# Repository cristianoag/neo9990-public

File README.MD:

# NEO9990

**NEO9990** is an open-hardware V9990 video-cartridge project for the MSX computer system. 

## Why NEO9990?

The Yamaha V9990 (the "E-VDP III") was designed in the early 1990s for the MSX3 standard that never reached the market. Its best-known home is the Sunrise GFX9000 cartridge from 1994, which gave MSX computers 2D graphics well beyond the built-in VDP, with high-resolution bitmap and tile modes and a hardware command engine. Its software library is small, and every title depends on that one chip.

[TRH9000](https://github.com/cristianoag/trh9000) was my first step: an open-source, real-chip GFX9000-compatible cartridge, documented so that anyone can build one. It works, but it relies on the Yamaha V9990 itself, and those chips are now super rare. They have been out of production for decades, and every cartridge built consumes a part that cannot be replaced. A design that needs one chip per board cannot be reproduced by the community at any useful scale, so we were kind of forced to develop emulation hardware.

NEO9990 is the answer to that shortage. Instead of hunting for scarce silicon, the emulation boards **reproduce the V9990 in firmware** on readily available, modern hardware, keeping the MSX side as close to the original as possible: the same I/O ports (60h–6Fh), the same register model and the same VRAM behaviour. Video output is digital (HDMI/DVI) rather than 15 kHz analog RGB, so it works with current displays.

NEO9990 is an open-source project and another contribution to the MSX community from **The Retro Hacker**. Build it, improve it, port it, and share what you learn.

## Implementation tracks

This repository holds three implementation tracks, from the original real-chip design to the emulation boards that remove the dependency on the V9990 supply:

| Implementation | Approach | Status |
| --- | --- | --- |
| [Real-chip](hardware/realchip/) | Uses a Yamaha V9990 and a dedicated HDMI conversion/output stage. | Hardware design and fabrication files are published. |
| [Orange Pi](hardware/orangepi/) | Replaces V9990 hardware with V9990 emulation on an Orange Pi Zero 2W, connected to the MSX bus through a CPLD. | Prototype; backed by test firmware, HDL, and protocol software. Not a finished cartridge. |
| [Core2350B](hardware/core2350b/) | Replaces V9990 hardware with emulation on a Waveshare Core2350B (RP2350B) wired directly to the MSX bus, with HSTX HDMI/DVI output and USB-C. | Rev 1.0 schematic, routed PCB and initial tests done. V9990 firmware v1.00. |

|  |  |
|:---:|:---:|
| Real-chip board, front | Real-chip board, rear |

|  |  |
|:---:|:---:|
| Orange Pi prototype rendering, front | Orange Pi prototype rendering, rear |

|  |  |
|:---:|:---:|
| Core2350B board rendering, front | Core2350B board rendering, rear |

## Implementations in this repository

### Real-chip NEO9990

The real-chip implementation is the hardware project under [`hardware/realchip`](hardware/realchip/). It uses the Yamaha V9990 device and includes a chip-based digital-video conversion stage for HDMI output.

- [Real-chip overview](docs/realchip.md)
- [KiCad project](hardware/realchip/neo9990/neo9990.kicad_pro)
- [KiCad schematic](hardware/realchip/neo9990/neo9990.kicad_sch)
- [KiCad PCB](hardware/realchip/neo9990/neo9990.kicad_pcb)
- [Production files](hardware/realchip/neo9990/production/)
- [Interactive BOM](hardware/realchip/neo9990/bom/ibom.html)

### Orange Pi NEO9990

The Orange Pi implementation is an experimental board under [`hardware/orangepi`](hardware/orangepi/). It targets bare-metal V9990 emulation on an Orange Pi Zero 2W and uses an EPM7160STC100-10 CPLD between the MSX bus and a 16-bit parallel GPIO mailbox.

The full MSX address bus, memory request, and slot select signals are available to the host for ROM and mapper services. CPLD profiles prepare V9990, ROM, and OPL4 decoding, although the current firmware implements only a limited V9990 bring-up subset.

- [Orange Pi overview (hardware and software)](docs/orangepi.md)
- [KiCad prototype project](hardware/orangepi/neo9990/neo9990.kicad_pro)
- [Prototype restrictions and validation notes](hardware/orangepi/neo9990/prototype-notes.txt)
- [GPIO assignment](hardware/orangepi/neo9990/gpio-map.csv)
- [Prototype BOM](hardware/orangepi/neo9990/bom.csv)
- [Assembly drawings](hardware/orangepi/neo9990/plots/)
- [3D previews](hardware/orangepi/neo9990/plots/prototype-3d.png)
- [CPLD source and protocol documentation](software/orangepi/cpld/README.txt)
- [Parallel host ABI](software/orangepi/host/README.txt)
- [Bare-metal bring-up firmware](software/orangepi/firmware/README.txt)

### Core2350B NEO9990

The Core2350B implementation is under [`hardware/core2350b`](hardware/core2350b/). A Waveshare Core2350B module is wired directly to the MSX slot without voltage translation, outputs HDMI/DVI from the RP2350 HSTX pins, and is programmed over USB-C. The board outline, edge connector and USB-C wiring come from the PicoVerse 2350 board.

Rev 1.0 has a finished schematic and a routed PCB, and initial tests have been done. The V9990 firmware builds with `make` from `software/core2350b/v9990`; the UF2 file is in [`firmware/`](firmware/).

- [Core2350B hardware](docs/core2350b-hardware.md)
- [Core2350B firmware](docs/core2350b-firmware.md)
- [KiCad project](hardware/core2350b/neo9990/neo9990.kicad_pro)
- [GPIO assignment](hardware/core2350b/neo9990/gpio-map.csv)

## Documentation

The explanatory documents for every implementation are in [`docs/`](docs/index.md).

## Repository layout

```text
docs/          documentation for each implementation
firmware/      ready-to-flash Core2350B firmware images (UF2)
hardware/
  realchip/    Yamaha V9990 implementation and HDMI conversion/output hardware
  orangepi/    Orange Pi Zero 2W / CPLD prototype
  core2350b/   Waveshare Core2350B (RP2350B) implementation
software/
  orangepi/    CPLD, host protocol, and firmware tests/supporting software
  core2350b/   V9990 firmware for the Core2350B board
```

Each implementation keeps its own hardware and implementation-specific software. Files under `software/orangepi` are the supporting prototype software for `hardware/orangepi`; they are not firmware for the real-chip board or the Core2350B board.

## Contributing

Contributions are welcome through issues and pull requests. Keep changes scoped to the correct implementation directory and state clearly whether they affect the real-chip board, the Orange Pi prototype, or a future track.

Hardware changes should include the corresponding fabrication/CAD outputs when applicable. Prototype software and HDL changes should include focused tests and should not claim unverified board-level operation.

## Sponsoring

You can support NEO9990 development through [GitHub Sponsors](https://github.com/sponsors/cristianoag).

## Third-party notices and references

The NEO9990 Core2350B firmware (`software/core2350b`) builds on the work below.
Source files that derive from it say so in their header comment.

* **Yamaha V9990 behaviour: openMSX**: Where the Yamaha V9990 Application Manual is silent, the V9990 core follows the
behaviour of openMSX (`src/video/v9990`, <https://github.com/openMSX/openMSX>), which is released under the GNU General Public License v2.

* **DVI output: pico-examples**: `common/dvi_out.c` is derived from the HSTX DVI example in <https://github.com/raspberrypi/pico-examples>. Copyright 2020 (c) Raspberry Pi (Trading) Ltd.

## License

This project is licensed under the [Creative Commons Attribution-NonCommercial-ShareAlike 4.0 International License](http://creativecommons.org/licenses/by-nc-sa/4.0/).

- You may remix and adapt the material with proper attribution.
- Derivative works must be shared under the same license.
- Commercial use is not permitted without explicit authorization.

See [LICENSE.txt](LICENSE.txt) for the complete license text.

The Orange Pi firmware and shared host protocol header are separately licensed under **GPL-2.0-only**. See the [firmware license and notices](software/orangepi/firmware/COPYING) and [openMSX provenance](software/orangepi/firmware/third_party/openmsx/PROVENANCE.txt).

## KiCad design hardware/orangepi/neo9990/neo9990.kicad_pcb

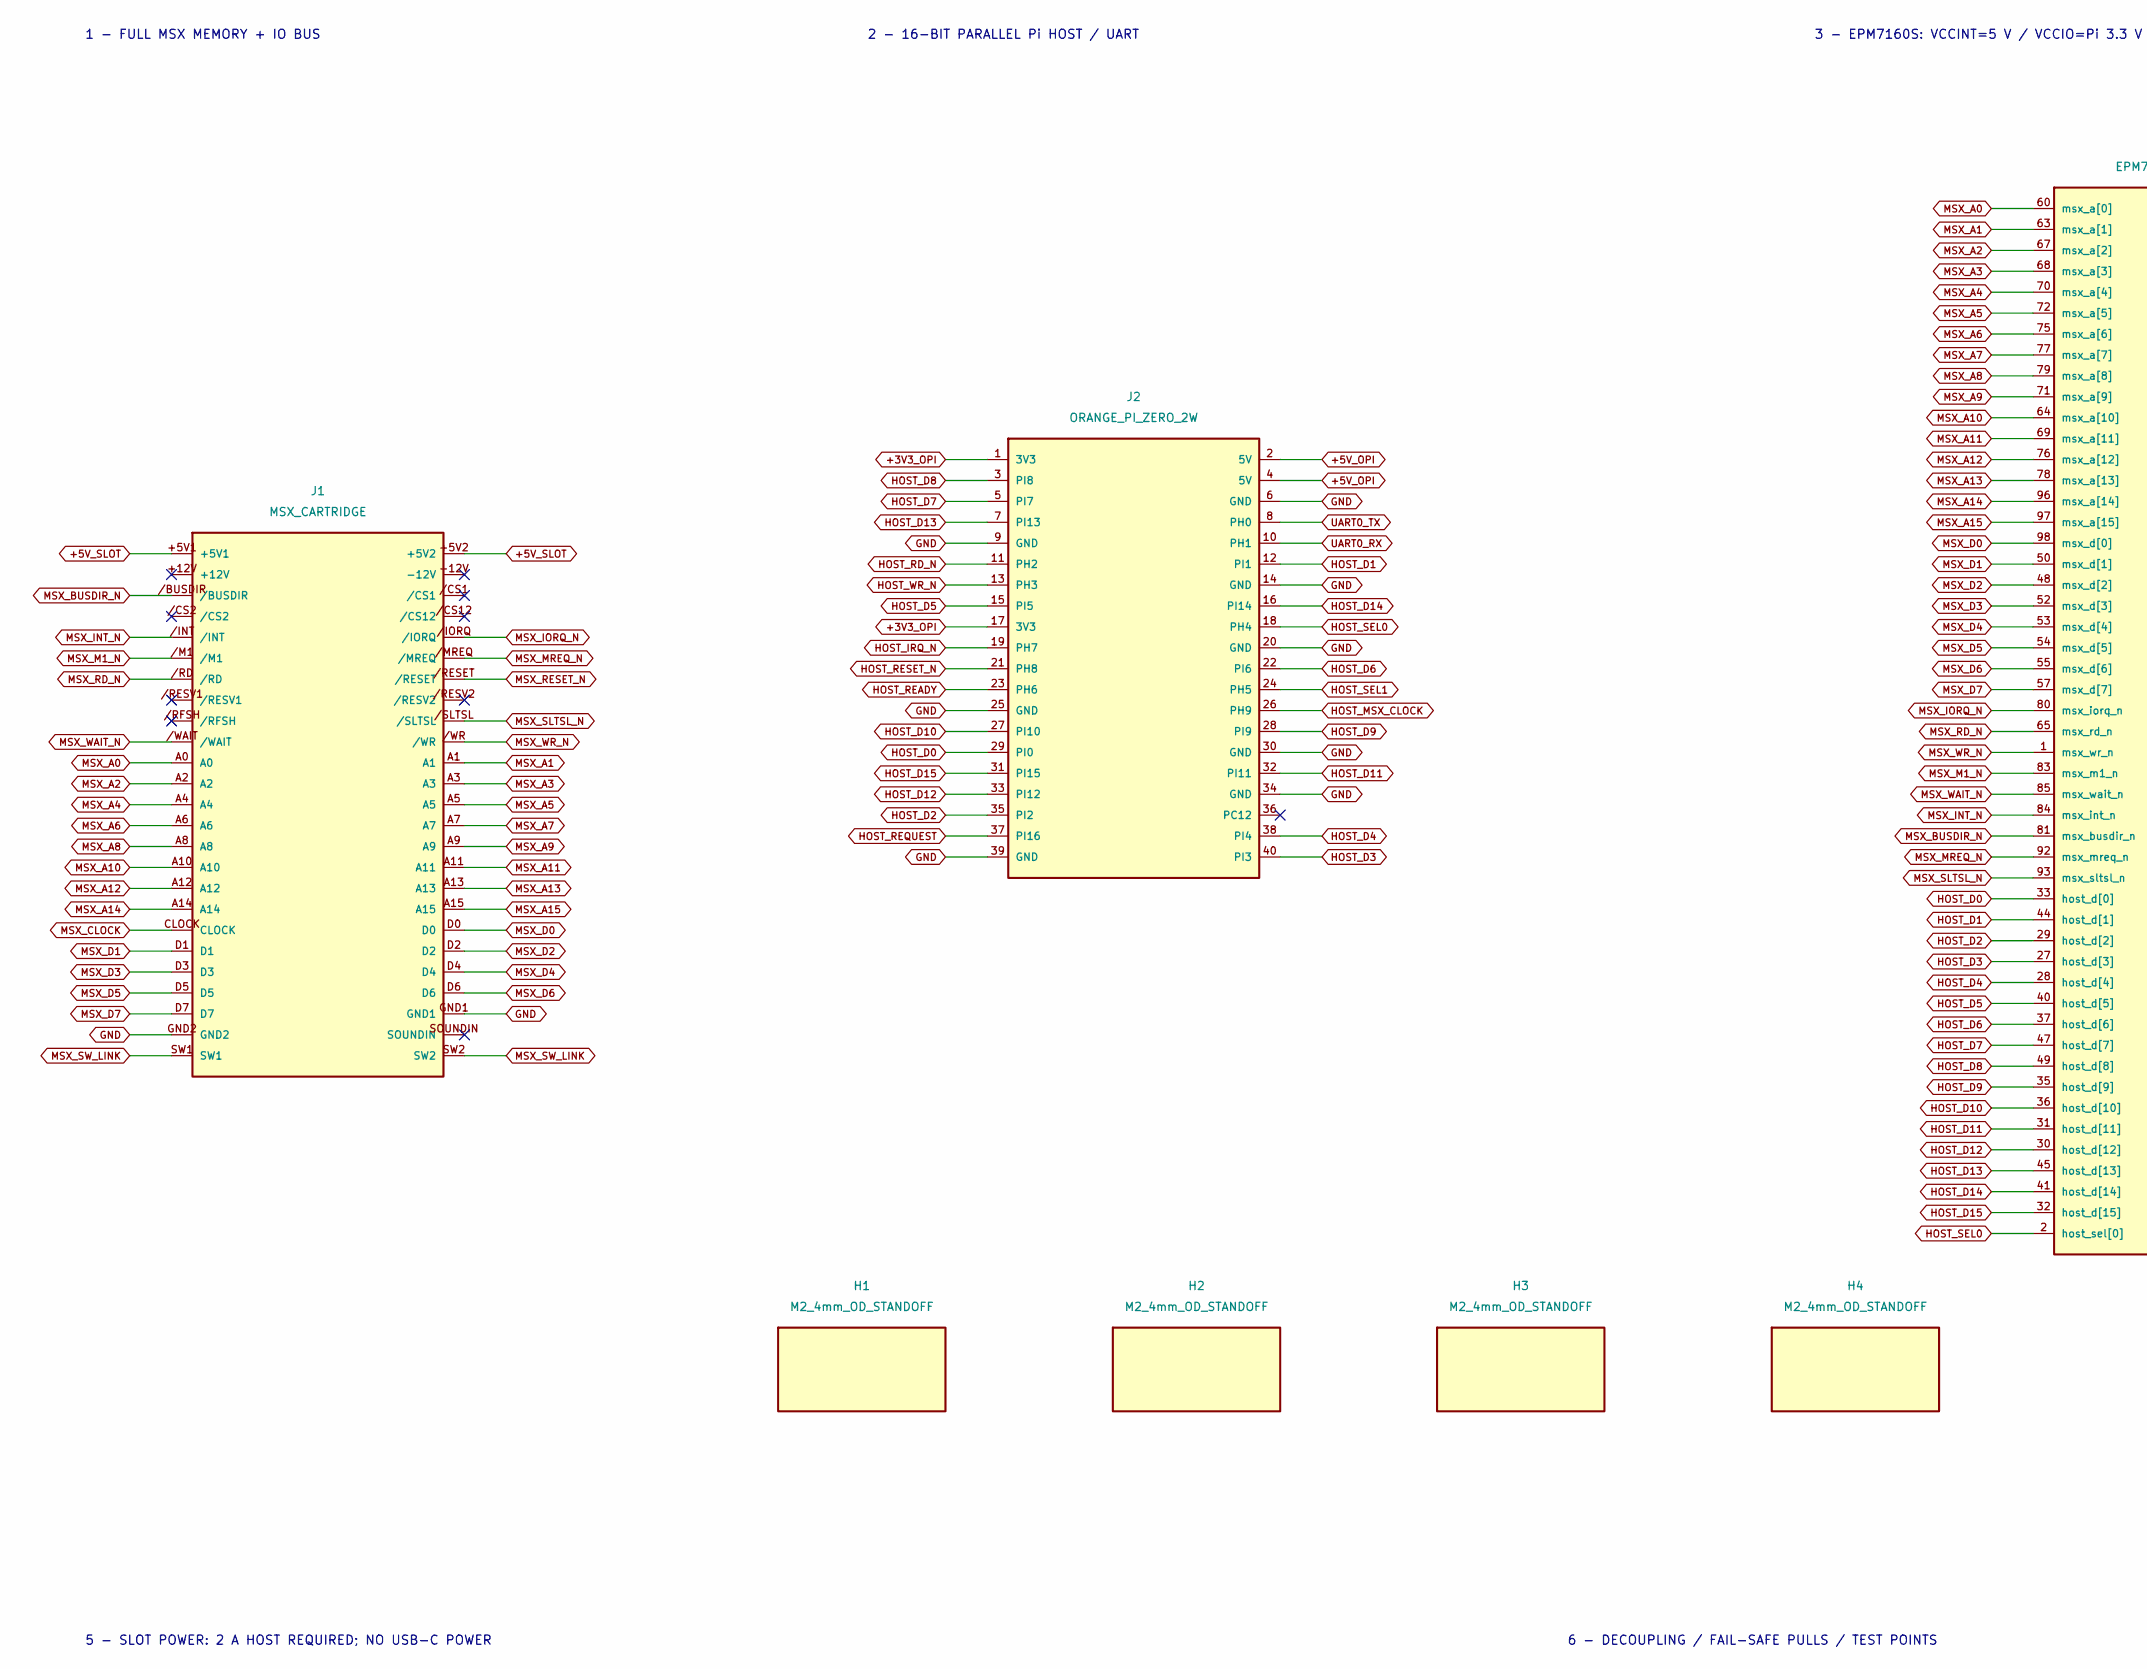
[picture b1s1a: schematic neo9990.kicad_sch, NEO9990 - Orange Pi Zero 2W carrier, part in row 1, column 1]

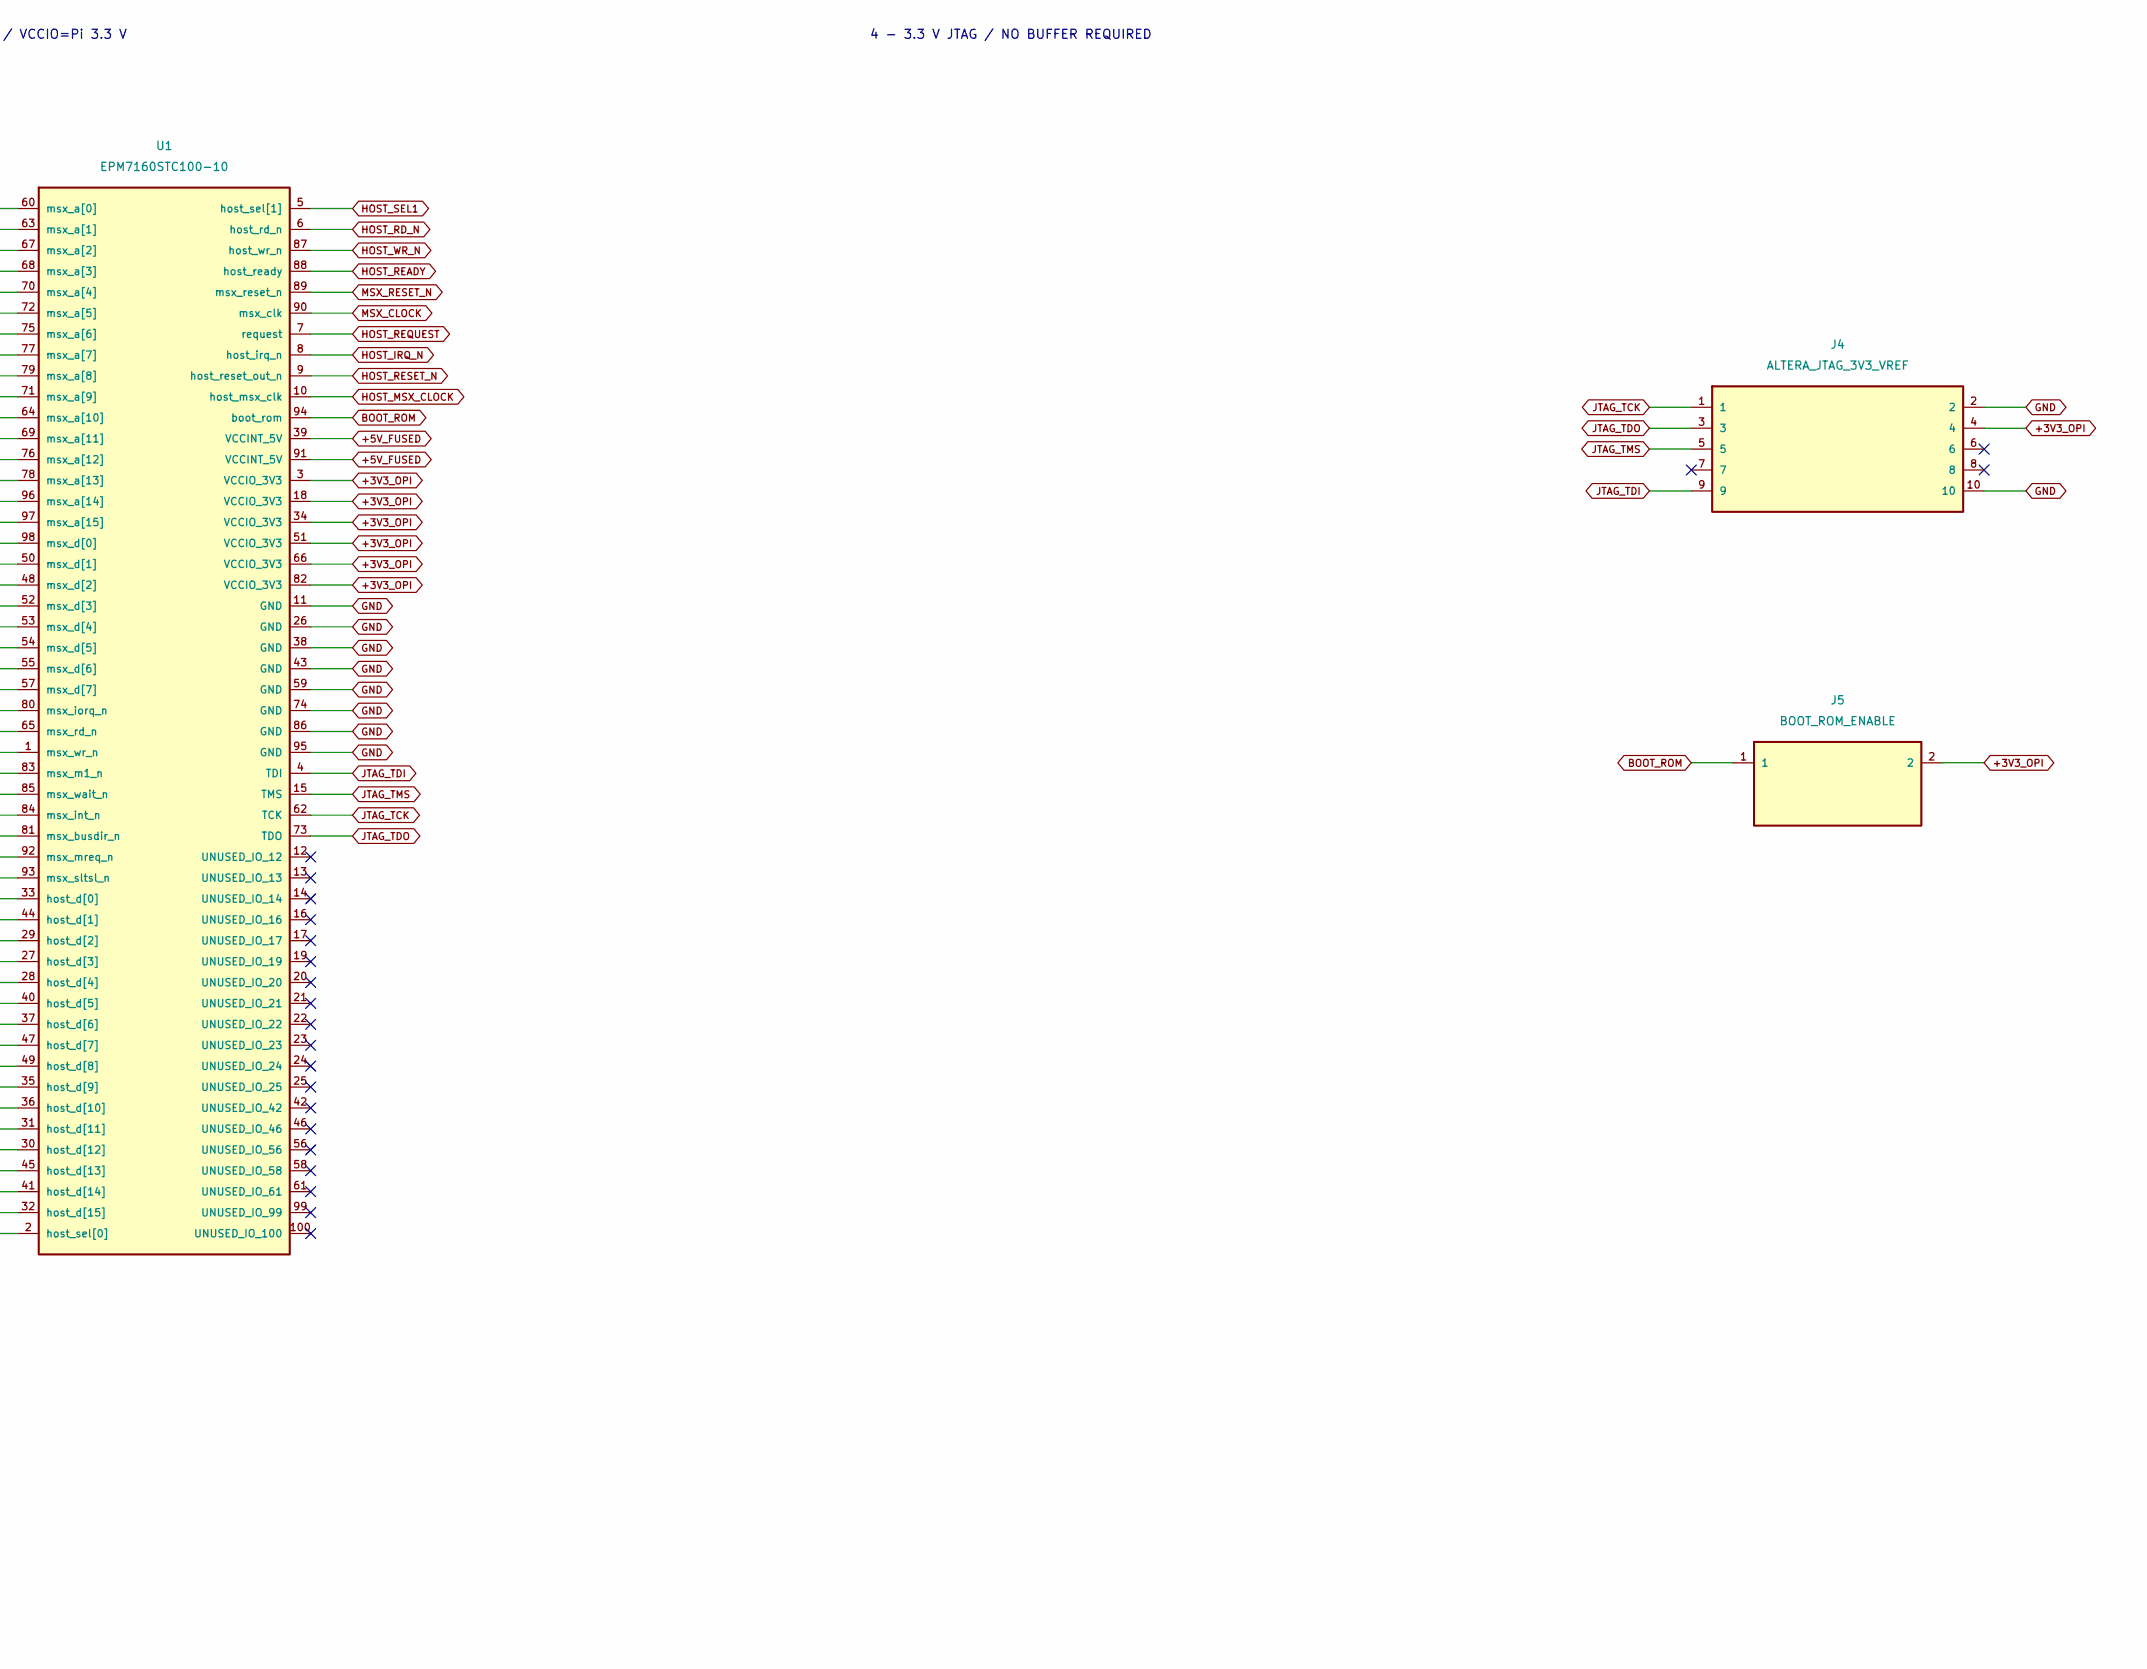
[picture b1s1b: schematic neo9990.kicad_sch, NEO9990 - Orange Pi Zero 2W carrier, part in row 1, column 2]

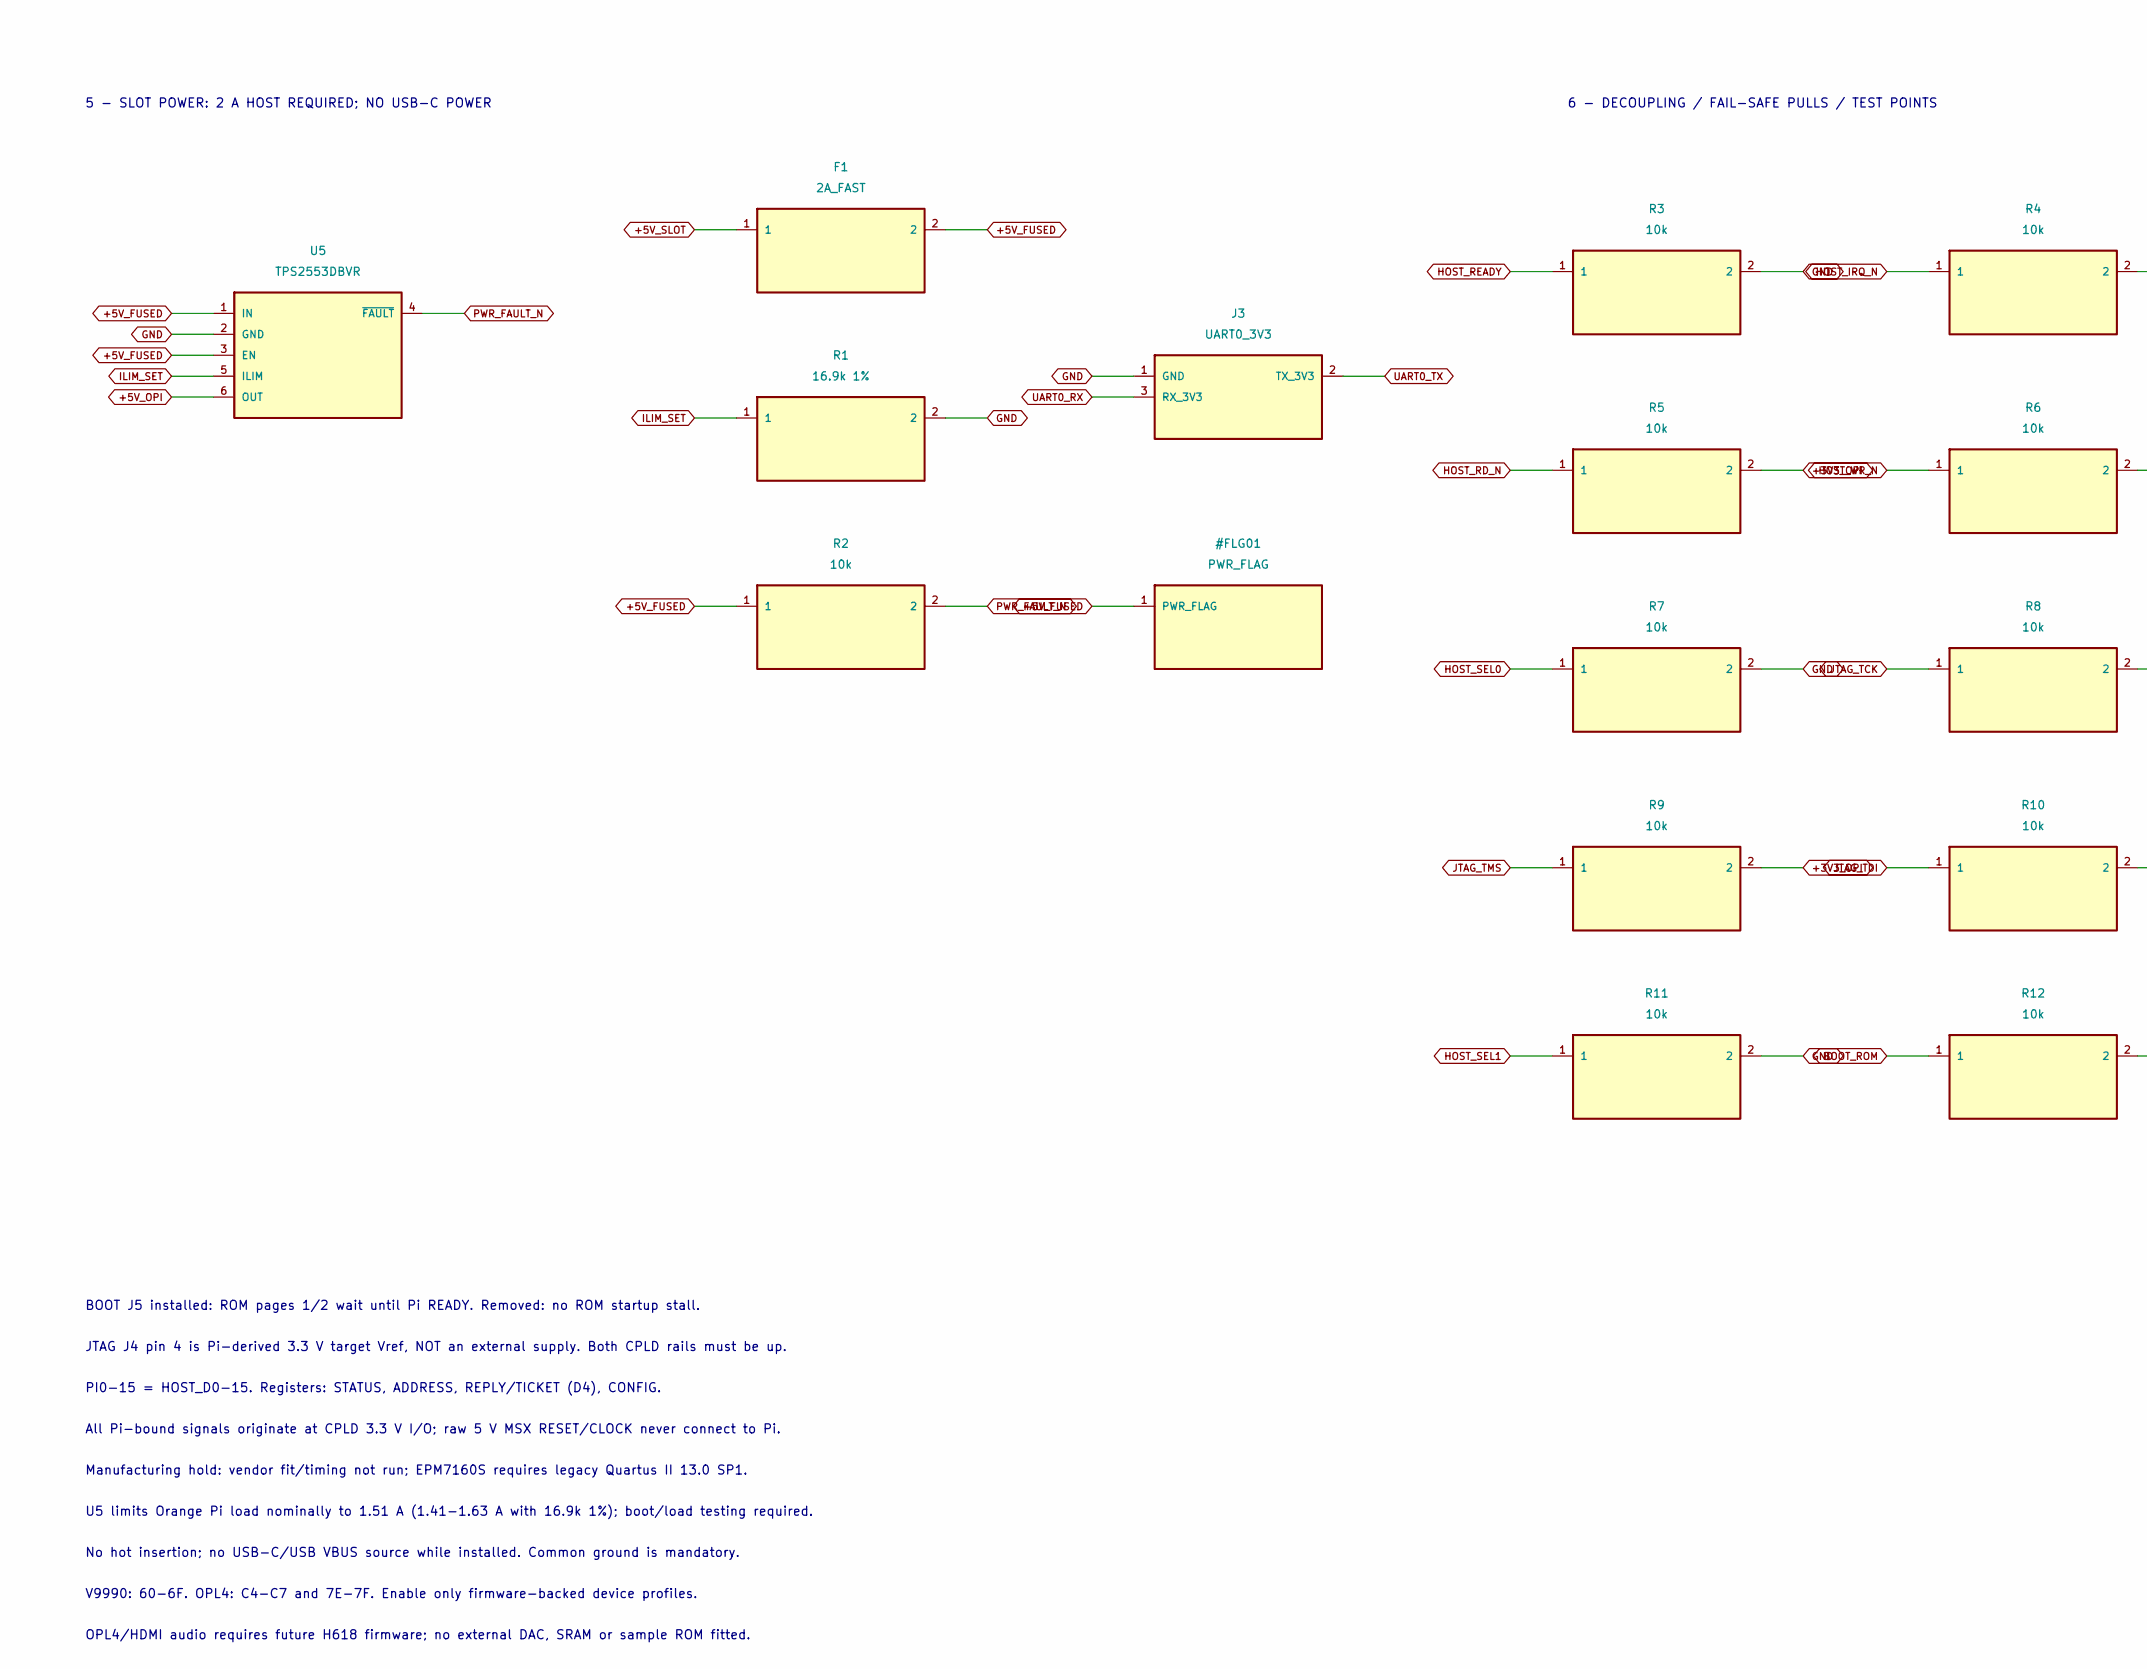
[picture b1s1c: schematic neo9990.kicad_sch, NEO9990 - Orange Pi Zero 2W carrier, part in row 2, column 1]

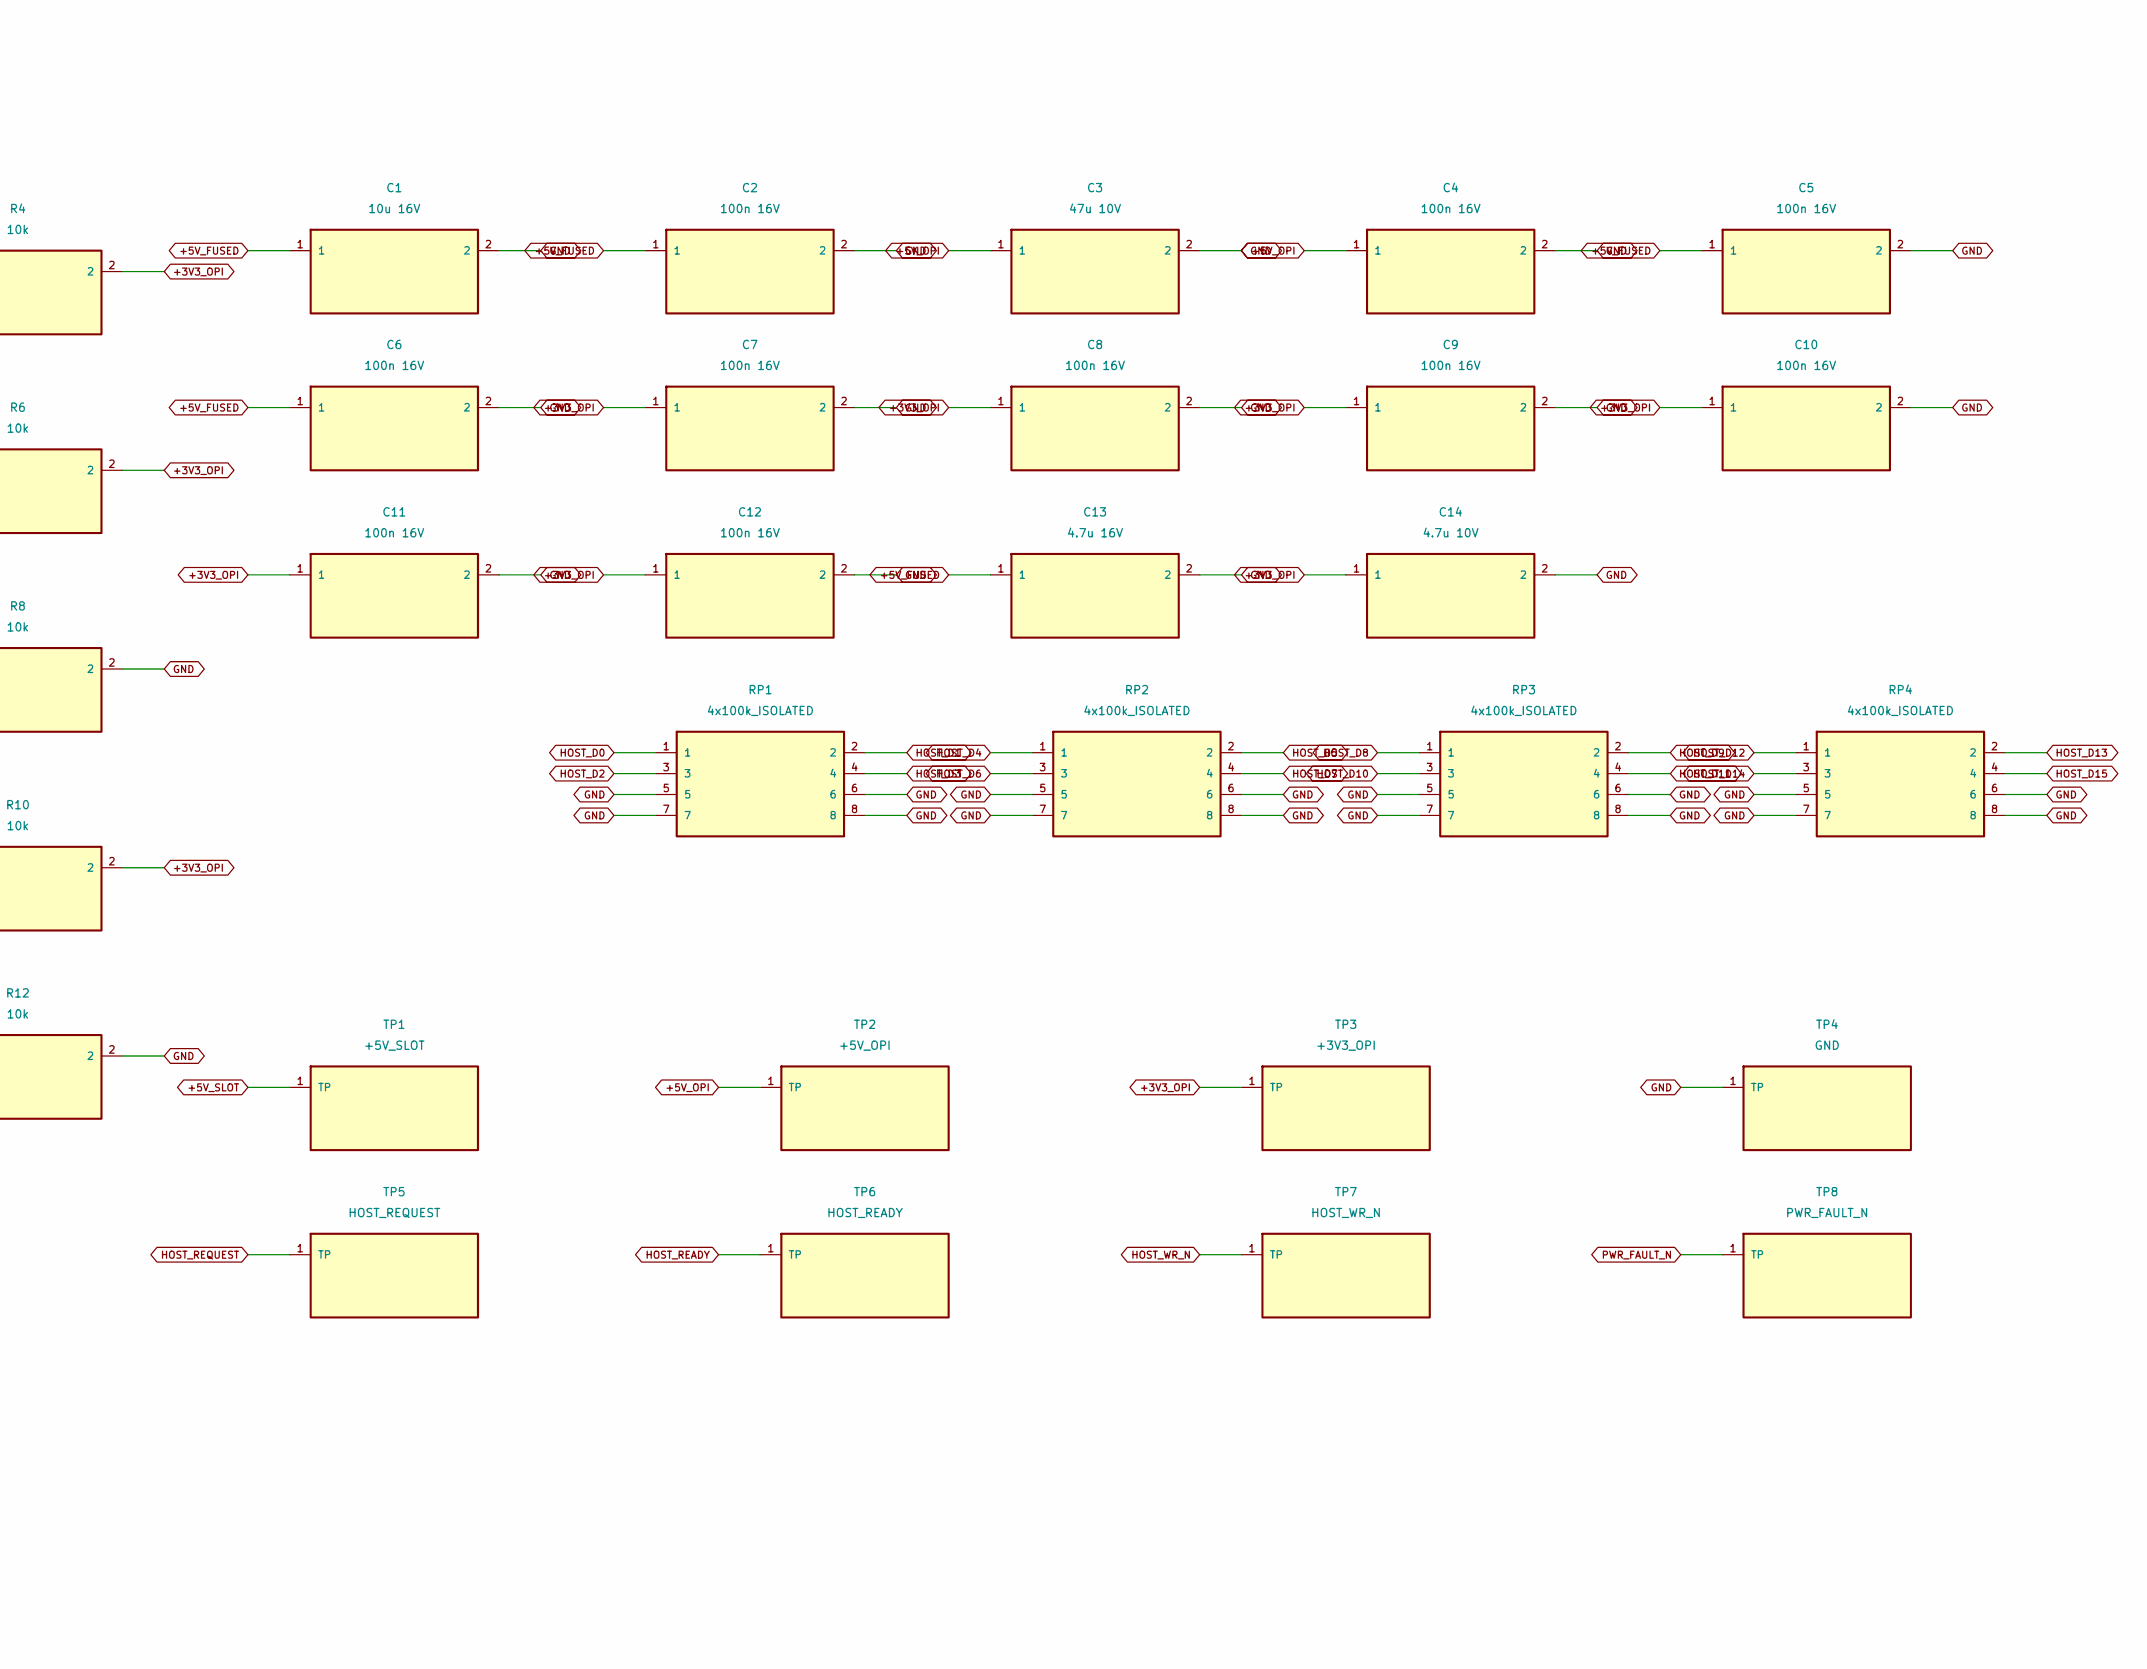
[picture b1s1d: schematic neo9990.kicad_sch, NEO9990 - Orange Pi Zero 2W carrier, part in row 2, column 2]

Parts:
C1: 10u 16V; C_0805_2012Metric
C2, C4, C5, C6, C7, C8, C9, C10, C11, C12: 100n 16V; C_0603_1608Metric
C3: 47u 10V; C_1210_3225Metric
C13: 4.7u 16V; C_0805_2012Metric
C14: 4.7u 10V; C_0805_2012Metric
F1: 2A_FAST; Fuse_1206_3216Metric; MPN 0467002.NR
H1, H2, H3, H4: M2_4mm_OD_STANDOFF; ModuleStandoff
J1: MSX_CARTRIDGE; MSX_Cartridge
J2: ORANGE_PI_ZERO_2W; OrangePi_Zero2W
J3: UART0_3V3; PinHeader_1x03_P2.54mm_Vertical
J4: ALTERA_JTAG_3V3_VREF; PinHeader_2x05_P2.54mm_Vertical
J5: BOOT_ROM_ENABLE; PinHeader_1x02_P2.54mm_Vertical
R1: 16.9k 1%; R_0603_1608Metric
R2, R3, R4, R5, R6, R7, R8, R9, R10, R11, R12: 10k; R_0603_1608Metric
RP1, RP2, RP3, RP4: 4x100k_ISOLATED; R_Array_Convex_4x0603
TP1: +5V_SLOT; TestPoint_Pad_D1.0mm
TP2: +5V_OPI; TestPoint_Pad_D1.0mm
TP3: +3V3_OPI; TestPoint_Pad_D1.0mm
TP4: GND; TestPoint_Pad_D1.0mm
TP5: HOST_REQUEST; TestPoint_Pad_D1.0mm
TP6: HOST_READY; TestPoint_Pad_D1.0mm
TP7: HOST_WR_N; TestPoint_Pad_D1.0mm
TP8: PWR_FAULT_N; TestPoint_Pad_D1.0mm
U1: EPM7160STC100-10; TQFP-100_14x14mm_P0.5mm; MPN EPM7160STC100-10
U5: TPS2553DBVR; SOT-23-6; MPN TPS2553DBVR

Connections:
+3V3_OPI: C7.1, C8.1, C9.1, C10.1, C11.1, C12.1, C14.1, J2.1 (3V3), J2.17 (3V3), J4.4, J5.2, R4.2, R5.2, R6.2, R9.2, R10.2, TP3.1, U1.3 (VCCIO_3V3), U1.18 (VCCIO_3V3), U1.34 (VCCIO_3V3), U1.51 (VCCIO_3V3), U1.66 (VCCIO_3V3), U1.82 (VCCIO_3V3)
+5V_FUSED: C1.1, C2.1, C5.1, C6.1, C13.1, F1.2, R2.1, U1.39 (VCCINT_5V), U1.91 (VCCINT_5V), U5.1 (IN), U5.3 (EN)
+5V_OPI: C3.1, C4.1, J2.2 (5V), J2.4 (5V), TP2.1, U5.6 (OUT)
+5V_SLOT: F1.1, J1.+5V1, J1.+5V2, TP1.1
BOOT_ROM: J5.1, R12.1, U1.94 (boot_rom)
GND: C1.2, C2.2, C3.2, C4.2, C5.2, C6.2, C7.2, C8.2, C9.2, C10.2, C11.2, C12.2, C13.2, C14.2, J1.GND1, J1.GND2, J2.6 (GND), J2.9 (GND), J2.14 (GND), J2.20 (GND), J2.25 (GND), J2.30 (GND), J2.34 (GND), J2.39 (GND), J3.1 (GND), J4.2, J4.10, R1.2, R3.2, R7.2, R8.2, R11.2, R12.2, RP1.5, RP1.6, RP1.7, RP1.8, RP2.5, RP2.6, RP2.7, RP2.8, RP3.5, RP3.6, RP3.7, RP3.8, RP4.5, RP4.6, RP4.7, RP4.8, TP4.1, U1.11 (GND), U1.26 (GND), U1.38 (GND), U1.43 (GND), U1.59 (GND), U1.74 (GND), U1.86 (GND), U1.95 (GND), U5.2 (GND)
HOST_D0: J2.29 (PI0), RP1.1, U1.33 (host_d[0])
HOST_D1: J2.12 (PI1), RP1.2, U1.44 (host_d[1])
HOST_D2: J2.35 (PI2), RP1.3, U1.29 (host_d[2])
HOST_D3: J2.40 (PI3), RP1.4, U1.27 (host_d[3])
HOST_D4: J2.38 (PI4), RP2.1, U1.28 (host_d[4])
HOST_D5: J2.15 (PI5), RP2.2, U1.40 (host_d[5])
HOST_D6: J2.22 (PI6), RP2.3, U1.37 (host_d[6])
HOST_D7: J2.5 (PI7), RP2.4, U1.47 (host_d[7])
HOST_D8: J2.3 (PI8), RP3.1, U1.49 (host_d[8])
HOST_D9: J2.28 (PI9), RP3.2, U1.35 (host_d[9])
HOST_D10: J2.27 (PI10), RP3.3, U1.36 (host_d[10])
HOST_D11: J2.32 (PI11), RP3.4, U1.31 (host_d[11])
HOST_D12: J2.33 (PI12), RP4.1, U1.30 (host_d[12])
HOST_D13: J2.7 (PI13), RP4.2, U1.45 (host_d[13])
HOST_D14: J2.16 (PI14), RP4.3, U1.41 (host_d[14])
HOST_D15: J2.31 (PI15), RP4.4, U1.32 (host_d[15])
HOST_IRQ_N: J2.19 (PH7), R4.1, U1.8 (host_irq_n)
HOST_MSX_CLOCK: J2.26 (PH9), U1.10 (host_msx_clk)
HOST_RD_N: J2.11 (PH2), R5.1, U1.6 (host_rd_n)
HOST_READY: J2.23 (PH6), R3.1, TP6.1, U1.88 (host_ready)
HOST_REQUEST: J2.37 (PI16), TP5.1, U1.7 (request)
HOST_RESET_N: J2.21 (PH8), U1.9 (host_reset_out_n)
HOST_SEL0: J2.18 (PH4), R7.1, U1.2 (host_sel[0])
HOST_SEL1: J2.24 (PH5), R11.1, U1.5 (host_sel[1])
HOST_WR_N: J2.13 (PH3), R6.1, TP7.1, U1.87 (host_wr_n)
ILIM_SET: R1.1, U5.5 (ILIM)
JTAG_TCK: J4.1, R8.1, U1.62 (TCK)
JTAG_TDI: J4.9, R10.1, U1.4 (TDI)
JTAG_TDO: J4.3, U1.73 (TDO)
JTAG_TMS: J4.5, R9.1, U1.15 (TMS)
MSX_A0: J1.A0, U1.60 (msx_a[0])
MSX_A1: J1.A1, U1.63 (msx_a[1])
MSX_A2: J1.A2, U1.67 (msx_a[2])
MSX_A3: J1.A3, U1.68 (msx_a[3])
MSX_A4: J1.A4, U1.70 (msx_a[4])
MSX_A5: J1.A5, U1.72 (msx_a[5])
MSX_A6: J1.A6, U1.75 (msx_a[6])
MSX_A7: J1.A7, U1.77 (msx_a[7])
MSX_A8: J1.A8, U1.79 (msx_a[8])
MSX_A9: J1.A9, U1.71 (msx_a[9])
MSX_A10: J1.A10, U1.64 (msx_a[10])
MSX_A11: J1.A11, U1.69 (msx_a[11])
MSX_A12: J1.A12, U1.76 (msx_a[12])
MSX_A13: J1.A13, U1.78 (msx_a[13])
MSX_A14: J1.A14, U1.96 (msx_a[14])
MSX_A15: J1.A15, U1.97 (msx_a[15])
MSX_BUSDIR_N: J1./BUSDIR, U1.81 (msx_busdir_n)
MSX_CLOCK: J1.CLOCK, U1.90 (msx_clk)
MSX_D0: J1.D0, U1.98 (msx_d[0])
MSX_D1: J1.D1, U1.50 (msx_d[1])
MSX_D2: J1.D2, U1.48 (msx_d[2])
MSX_D3: J1.D3, U1.52 (msx_d[3])
MSX_D4: J1.D4, U1.53 (msx_d[4])
MSX_D5: J1.D5, U1.54 (msx_d[5])
MSX_D6: J1.D6, U1.55 (msx_d[6])
MSX_D7: J1.D7, U1.57 (msx_d[7])
MSX_INT_N: J1./INT, U1.84 (msx_int_n)
MSX_IORQ_N: J1./IORQ, U1.80 (msx_iorq_n)
MSX_M1_N: J1./M1, U1.83 (msx_m1_n)
MSX_MREQ_N: J1./MREQ, U1.92 (msx_mreq_n)
MSX_RD_N: J1./RD, U1.65 (msx_rd_n)
MSX_RESET_N: J1./RESET, U1.89 (msx_reset_n)
MSX_SLTSL_N: J1./SLTSL, U1.93 (msx_sltsl_n)
MSX_SW_LINK: J1.SW1, J1.SW2
MSX_WAIT_N: J1./WAIT, U1.85 (msx_wait_n)
MSX_WR_N: J1./WR, U1.1 (msx_wr_n)
PWR_FAULT_N: R2.2, TP8.1, U5.4 (~FAULT)
UART0_RX: J2.10 (PH1), J3.3 (RX_3V3)
UART0_TX: J2.8 (PH0), J3.2 (TX_3V3)

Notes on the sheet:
1 - FULL MSX MEMORY + IO BUS
2 - 16-BIT PARALLEL Pi HOST / UART
3 - EPM7160S: VCCINT=5 V / VCCIO=Pi 3.3 V
4 - 3.3 V JTAG / NO BUFFER REQUIRED
5 - SLOT POWER: 2 A HOST REQUIRED; NO USB-C POWER
6 - DECOUPLING / FAIL-SAFE PULLS / TEST POINTS
BOOT J5 installed: ROM pages 1/2 wait until Pi READY. Removed: no ROM startup stall.
JTAG J4 pin 4 is Pi-derived 3.3 V target Vref, NOT an external supply. Both CPLD rails must be up.
PI0-15 = HOST_D0-15. Registers: STATUS, ADDRESS, REPLY/TICKET (D4), CONFIG.
All Pi-bound signals originate at CPLD 3.3 V I/O; raw 5 V MSX RESET/CLOCK never connect to Pi.
Manufacturing hold: vendor fit/timing not run; EPM7160S requires legacy Quartus II 13.0 SP1.
U5 limits Orange Pi load nominally to 1.51 A (1.41-1.63 A with 16.9k 1%); boot/load testing required.
No hot insertion; no USB-C/USB VBUS source while installed. Common ground is mandatory.
V9990: 60-6F. OPL4: C4-C7 and 7E-7F. Enable only firmware-backed device profiles.
OPL4/HDMI audio requires future H618 firmware; no external DAC, SRAM or sample ROM fitted.
